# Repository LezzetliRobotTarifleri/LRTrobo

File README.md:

# LRTrobo 
Lezzetli Robot Tarifleri YouTube kanalında, takipçiler ile birlikte çizilmiş basit bir robot kartı. Amaç EAGLE mekaniklerine alışmak ve yavaş yavaş zorluğu arttırmak.

[Sıfırdan! Basit Eğitim Robotu Çizip, Üretime Gönderiyoruz](https://lezzetlirobottarifleri.com/sifirdan-basit-egitim-robotu-cizip-uretime-gonderiyoruz/).

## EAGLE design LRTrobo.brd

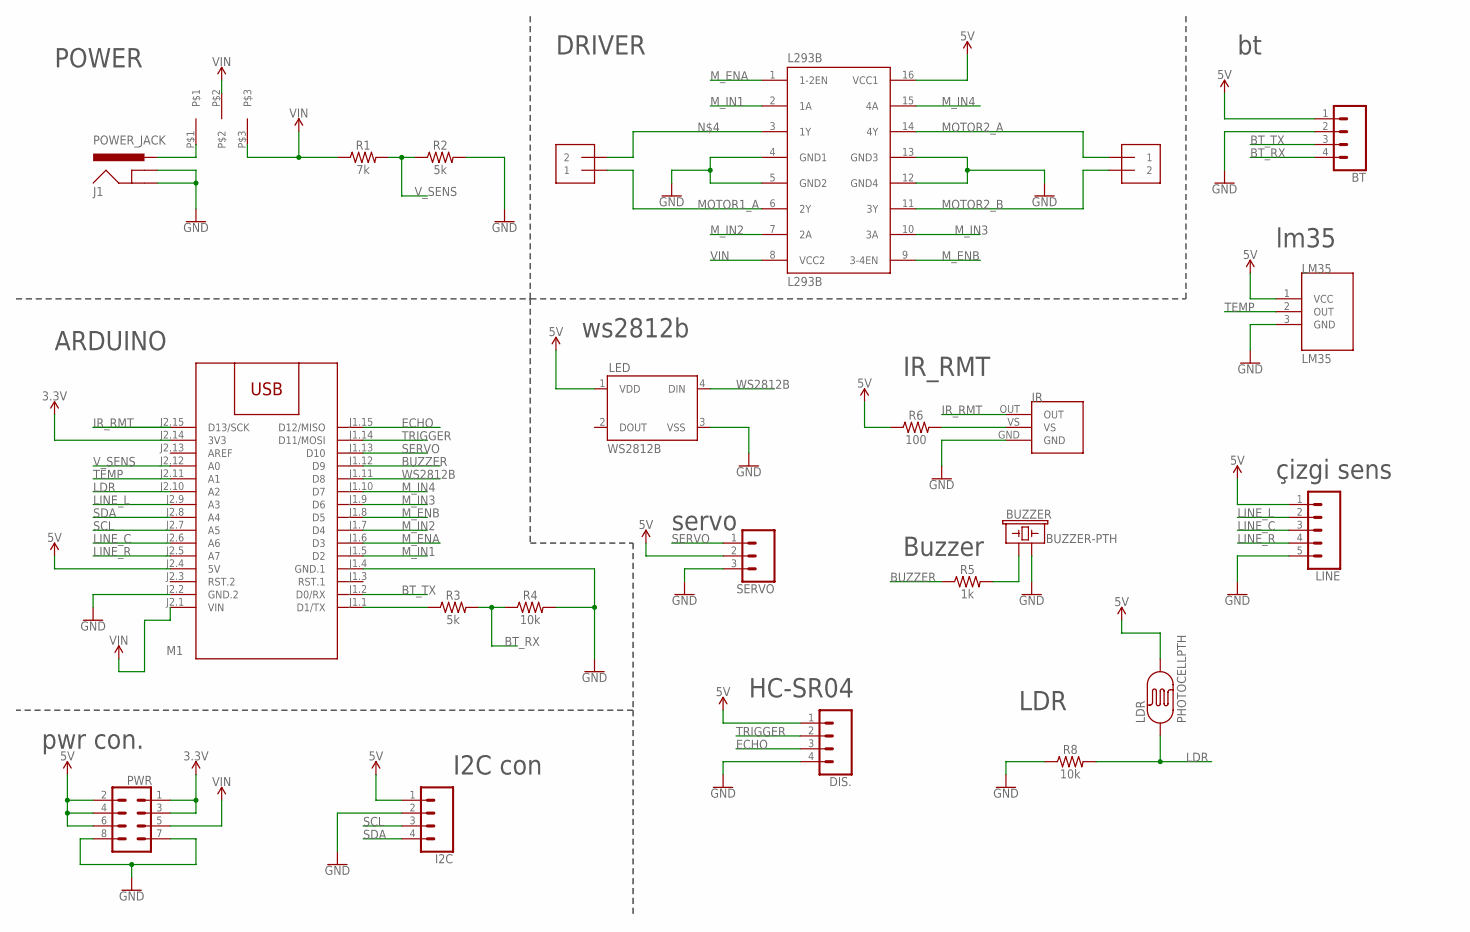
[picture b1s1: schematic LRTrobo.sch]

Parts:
BT: CONN_04; 1X04
BUZZER: BUZZER-PTH; BUZZER-12MM
DIS.: CONN_04; 1X04
I2C: CONN_04; 1X04
IR: TSOP2238THT; TSOP2238
J1: POWER_JACK; POWER_JACK_PTH
L293B: L293B; DIL16
LDR: PHOTOCELLPTH; PHOTOCELL
LED: WS2812B
LINE: CONN_05; 1X05
LM35: LM35; TO-92
M1: ARDUINO-NANO
MPOWER, MPOWER1: 1X2-3.5MM
PWR: CONN_04X2; 2X4
R1: 7k; AXIAL-0.3
R2, R3: 5k; AXIAL-0.3
R4, R8: 10k; AXIAL-0.3
R5: 1k; AXIAL-0.3
R6: 100; AXIAL-0.3
SERVO: CONN_03; 1X03
SW1: SW1

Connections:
3.3V: M1.J2.14 (3V3), PWR.1, PWR.3
5V: BT.1, DIS..1, I2C.1, L293B.16 (VCC1), LDR.2, LED.1 (VDD), LINE.1, LM35.1 (VCC), M1.J2.4 (5V), PWR.2, PWR.4, PWR.6, R6.P$1 (1), SERVO.2
BT_RX: BT.4, R3.P$2 (2), R4.P$1 (1)
BT_TX: BT.3, M1.J1.2 (D0/RX)
BUZZER: M1.J1.12 (D9), R5.P$1 (1)
ECHO: DIS..3, M1.J1.15 (D12/MISO)
GND: BT.2, BUZZER.- (2), DIS..4, I2C.2, IR.GND, J1.GND, J1.GNDBREAK, L293B.4 (GND1), L293B.5 (GND2), L293B.12 (GND4), L293B.13 (GND3), LED.3 (VSS), LINE.5, LM35.3 (GND), M1.J1.4 (GND.1), M1.J2.2 (GND.2), PWR.7, PWR.8, R2.P$2 (2), R4.P$2 (2), R8.P$1 (1), SERVO.3
IR_RMT: IR.OUT, M1.J2.15 (D13/SCK)
LDR: LDR.1, M1.J2.10 (A2), R8.P$2 (2)
LINE_C: LINE.3, M1.J2.6 (A6)
LINE_L: LINE.2, M1.J2.9 (A3)
LINE_R: LINE.4, M1.J2.5 (A7)
MOTOR1_A: L293B.6 (2Y), MPOWER.1
MOTOR2_A: L293B.14 (4Y), MPOWER1.1
MOTOR2_B: L293B.11 (3Y), MPOWER1.2
M_ENA: L293B.1 (1-2EN), M1.J1.6 (D3)
M_ENB: L293B.9 (3-4EN), M1.J1.8 (D5)
M_IN1: L293B.2 (1A), M1.J1.5 (D2)
M_IN2: L293B.7 (2A), M1.J1.7 (D4)
M_IN3: L293B.10 (3A), M1.J1.9 (D6)
M_IN4: L293B.15 (4A), M1.J1.10 (D7)
unnamed: M1.J1.1 (D1/TX), R3.P$1 (1)
unnamed: BUZZER.+ (1), R5.P$2 (2)
unnamed: IR.VS, R6.P$2 (2)
unnamed: L293B.3 (1Y), MPOWER.2
unnamed: J1.PWR, SW1.P$1
SCL: I2C.3, M1.J2.7 (A5)
SDA: I2C.4, M1.J2.8 (A4)
SERVO: M1.J1.13 (D10), SERVO.1
TEMP: LM35.2 (OUT), M1.J2.11 (A1)
TRIGGER: DIS..2, M1.J1.14 (D11/MOSI)
VIN: L293B.8 (VCC2), M1.J2.1 (VIN), PWR.5, R1.P$1 (1), SW1.P$2, SW1.P$3
V_SENS: M1.J2.12 (A0), R1.P$2 (2), R2.P$1 (1)
WS2812B: LED.4 (DIN), M1.J1.11 (D8)

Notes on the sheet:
POWER
ARDUINO
DRIVER
ws2812b
IR_RMT
Buzzer
servo
HC-SR04
LDR
I2C con
pwr con.
lm35
çizgi sens

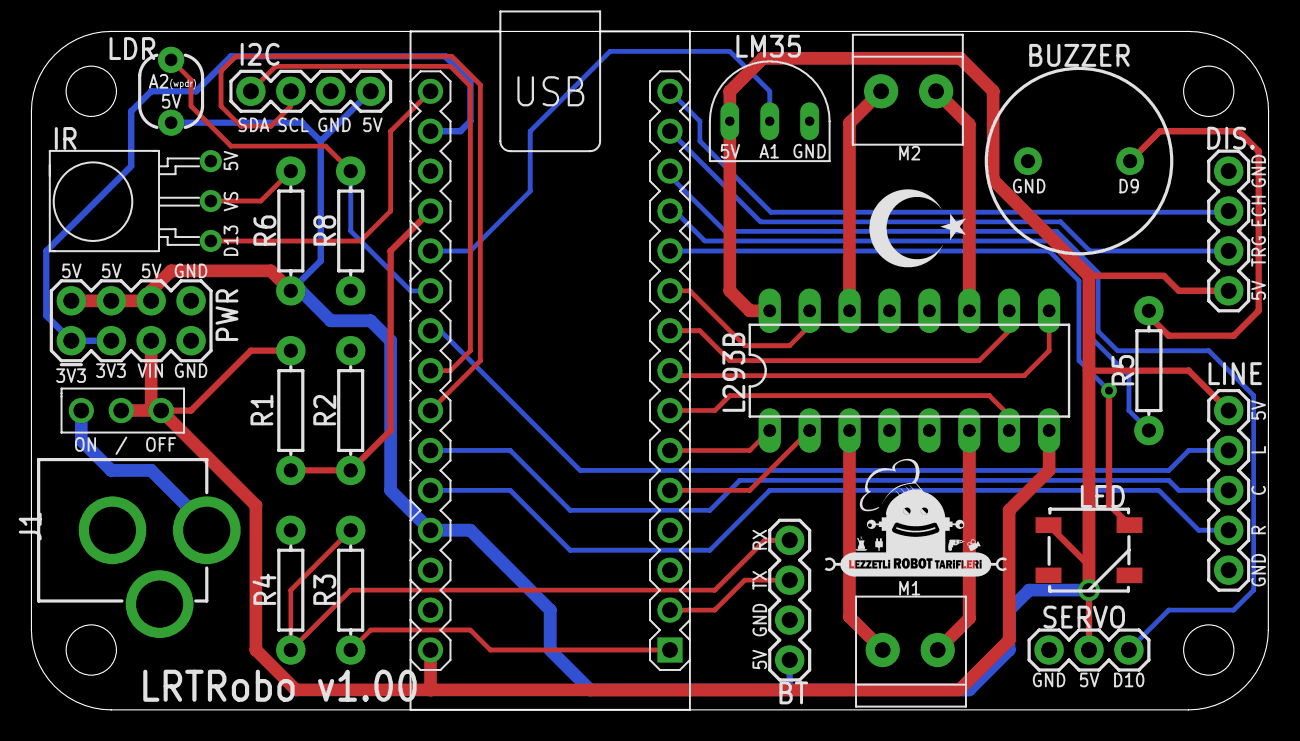
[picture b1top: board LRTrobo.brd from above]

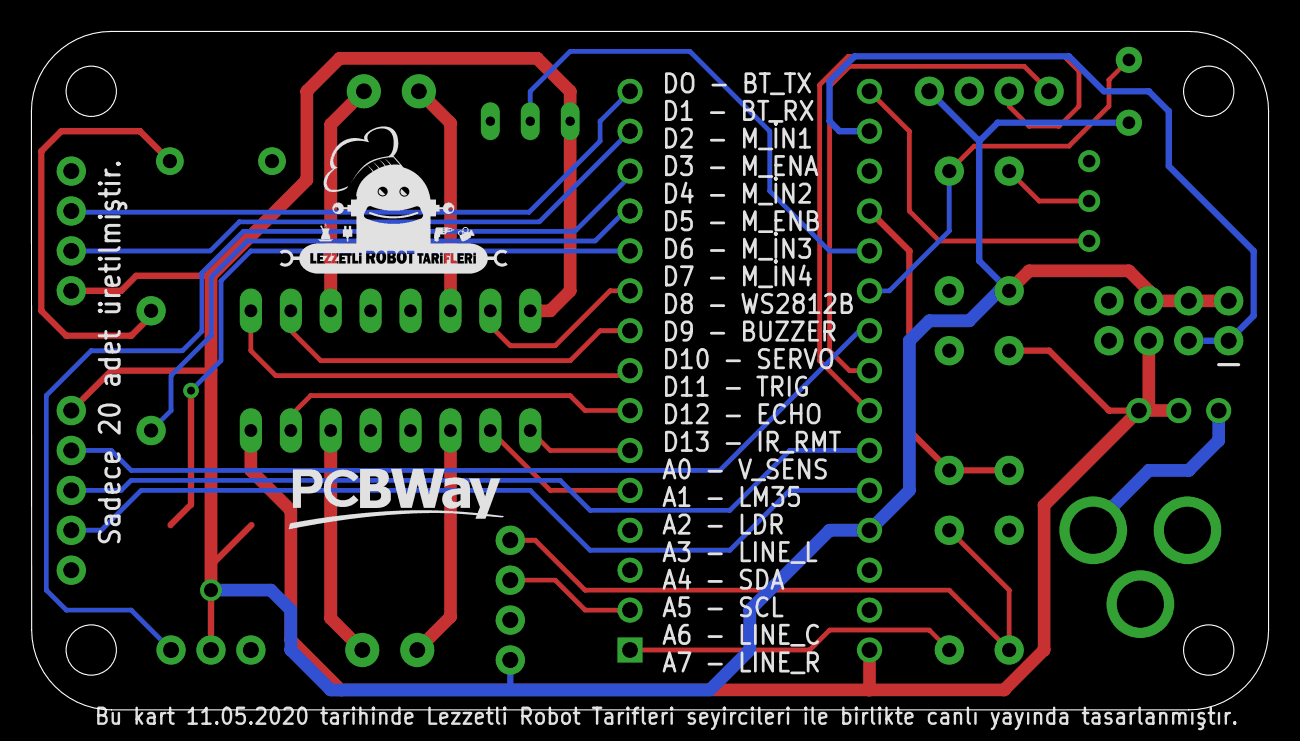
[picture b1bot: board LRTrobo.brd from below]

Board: 2 copper layers, 78.7 x 43.2 mm, 28 parts (2 on the bottom side), 34 nets.

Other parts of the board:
U$1: LRT-LOGO-0,0125-B
U$2: LOGO0.001
U$3: PCBWAY_LOGO_0.01
U$5: TR_MINI

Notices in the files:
parts and their libraries:
SparkFun-Connectors: Licensing: Creative Commons ShareAlike 4.0 International - https://creativecommons.org/licenses/by-sa/4.0
SparkFun-LED: Licensing: CC v3.0 Share-Alike You are welcome to use this library for commercial purposes.
